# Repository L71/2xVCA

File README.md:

2 channel VCA module for Eurorack. 

LM13700 based VCA. Two separate channels. 
The VCA CV input is biased to about 8V when no plug is in the CV input (so VCA is open). 

This PCB and front panel drawings are released under the Creative Commons CC-BY-SA 4.0 license.

** Note: the SMD version of the module has the potentionmeters in the opposite direction of the usual. Use knobs that match (or pots with round or T18 shafts).

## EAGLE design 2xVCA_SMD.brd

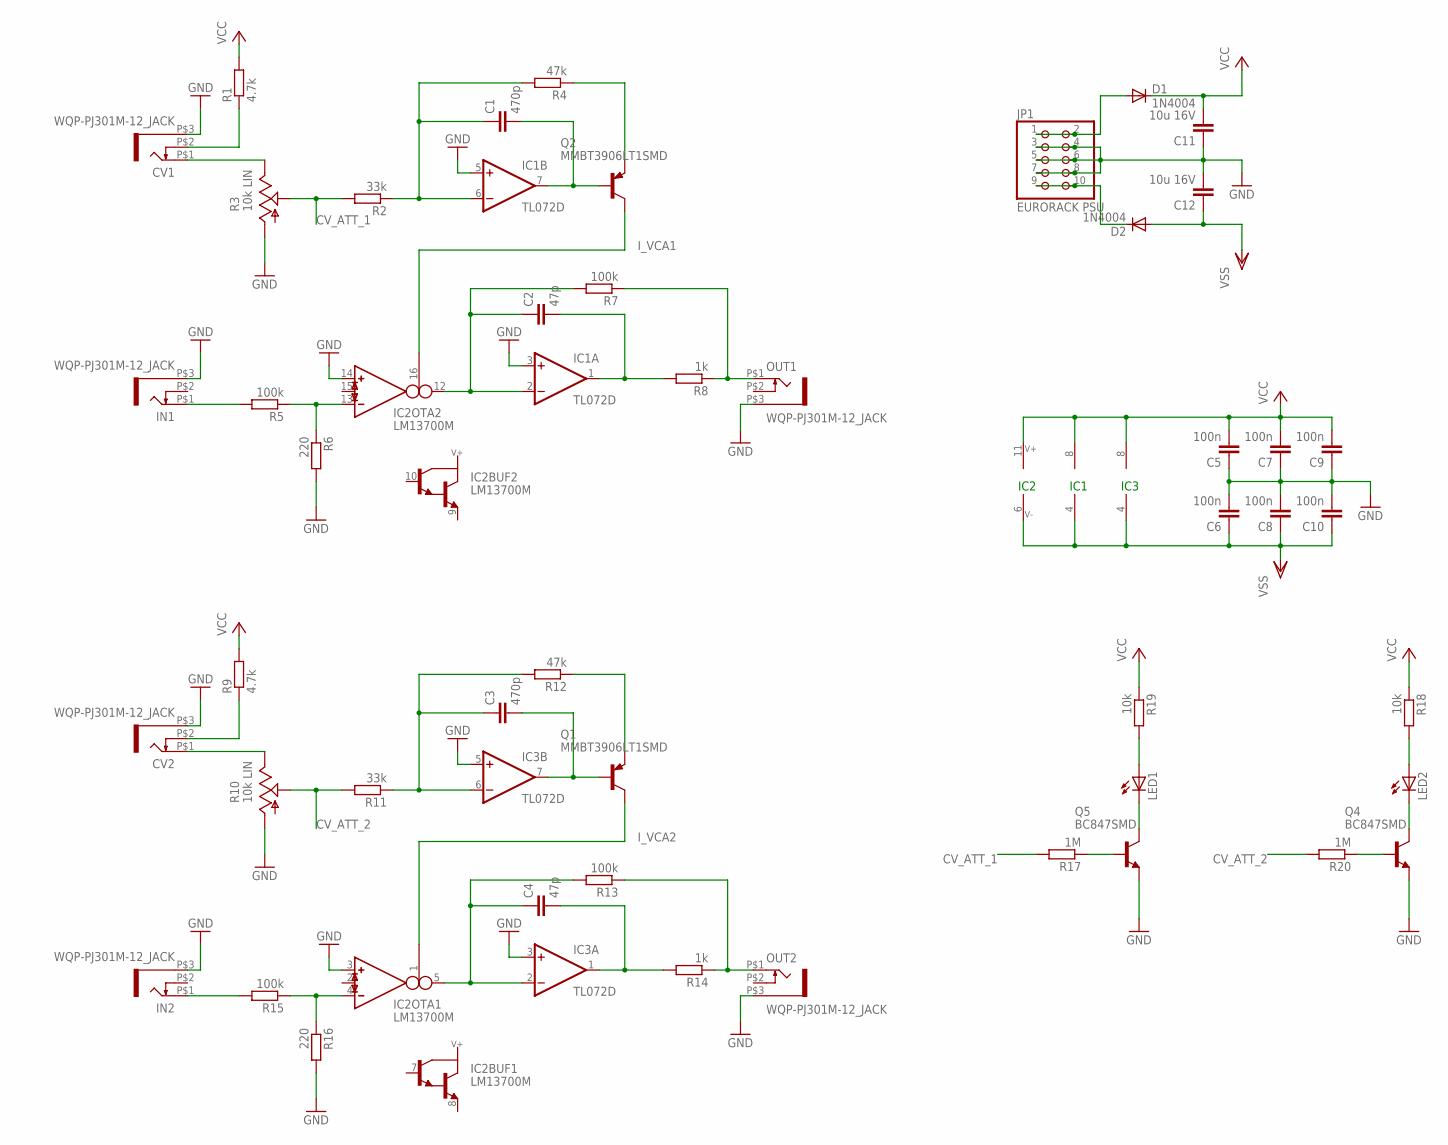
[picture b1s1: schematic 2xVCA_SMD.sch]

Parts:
C1, C3: 470p; C0603K
C2, C4: 47p; C0603K
C5, C6, C7, C8, C9, C10: 100n; C0603K
C11, C12: 10u 16V; C1206K
CV1, CV2: WQP-PJ301M-12_JACK
D1, D2: 1N4004; DO214AA
IC1, IC3: TL072D; SO08
IC2: LM13700M; SO16
IN1, IN2: WQP-PJ301M-12_JACK
JP1: EURORACK PSU; 2X05
LED1, LED2: LED3MM
OUT1, OUT2: WQP-PJ301M-12_JACK
Q1, Q2: MMBT3906LT1SMD; SOT23-BEC
Q4, Q5: BC847SMD; SOT23
R1, R9: 4.7k; R0603
R2, R11: 33k; R0603
R3, R10: 10k LIN; ALPS_POT_VERTICAL
R4, R12: 47k; R0603
R5, R7, R13, R15: 100k; R0603
R6, R16: 220; R0603
R8, R14: 1k; R0603
R17, R20: 1M; R0603
R18, R19: 10k; R0603

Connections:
CV_ATT_1: R2.2, R3.P$2 (S), R17.2
CV_ATT_2: R10.P$2 (S), R11.2, R20.2
GND: C5.1, C6.2, C7.1, C8.2, C9.1, C10.2, C11.1, C12.2, CV1.P$3 (1), CV2.P$3 (1), IC1.3 (+IN), IC1.5 (+IN), IC2.3 (IN_P), IC2.14 (IN_P), IC3.3 (+IN), IC3.5 (+IN), IN1.P$3 (1), IN2.P$3 (1), JP1.3, JP1.4, JP1.5, JP1.6, JP1.7, JP1.8, OUT1.P$3 (1), OUT2.P$3 (1), Q4.2 (E), Q5.2 (E), R3.P$3 (A), R6.2, R10.P$3 (A), R16.2
I_VCA1: IC2.16 (I_BIAS), Q2.C
I_VCA2: IC2.1 (I_BIAS), Q1.C
unnamed: IN2.P$1 (2), R15.2
unnamed: CV1.P$2 (3), R1.1
unnamed: CV1.P$1 (2), R3.P$1 (E)
unnamed: Q5.1 (B), R17.1
unnamed: C1.1, IC1.6 (-IN), R2.1, R4.2
unnamed: C2.1, IC1.2 (-IN), IC2.12 (OUT), R7.2
unnamed: C1.2, IC1.7 (OUT), Q2.B
unnamed: Q2.E, R4.1
unnamed: IC2.13 (IN_N), R5.1, R6.1
unnamed: IC2.4 (IN_N), R15.1, R16.1
unnamed: IN1.P$1 (2), R5.2
unnamed: C2.2, IC1.1 (OUT), R8.2
unnamed: OUT1.P$1 (2), R7.1, R8.1
unnamed: C4.1, IC2.5 (OUT), IC3.2 (-IN), R13.2
unnamed: CV2.P$2 (3), R9.1
unnamed: CV2.P$1 (2), R10.P$1 (E)
unnamed: LED1.A, R19.2
unnamed: C3.1, IC3.6 (-IN), R11.1, R12.2
unnamed: OUT2.P$1 (2), R13.1, R14.1
unnamed: C3.2, IC3.7 (OUT), Q1.B
unnamed: Q1.E, R12.1
unnamed: C4.2, IC3.1 (OUT), R14.2
unnamed: LED1.K (C), Q5.3 (C)
unnamed: LED2.A, R18.2
unnamed: LED2.K (C), Q4.3 (C)
unnamed: Q4.1 (B), R20.1
unnamed: D1.A, JP1.1, JP1.2
unnamed: D2.C, JP1.9, JP1.10
VCC: C5.2, C7.2, C9.2, C11.2, D1.C, IC1.8 (V+), IC2.11 (V+), IC3.8 (V+), R1.2, R9.2, R18.1, R19.1
VSS: C6.1, C8.1, C10.1, C12.1, D2.A, IC1.4 (V-), IC2.6 (V-), IC3.4 (V-)

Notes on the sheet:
IC1
IC2
IC3

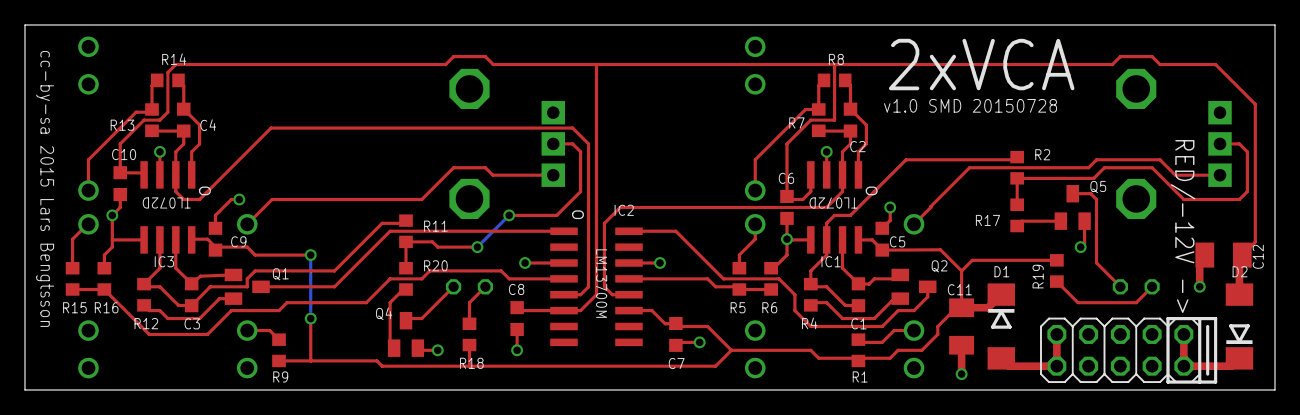
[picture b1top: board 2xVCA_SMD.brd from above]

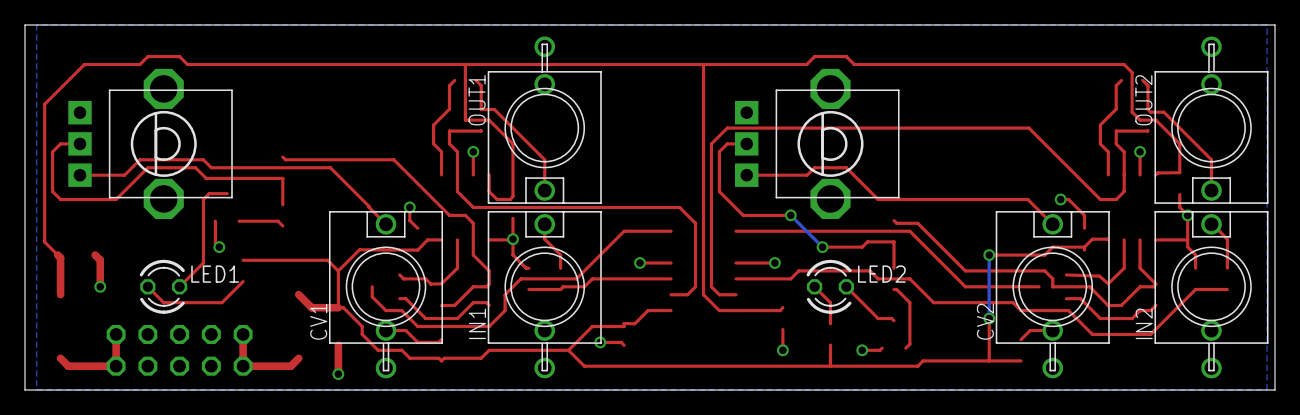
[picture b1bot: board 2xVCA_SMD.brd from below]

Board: 2 copper layers, 100.0 x 29.2 mm, 50 parts (10 on the bottom side), 35 nets.

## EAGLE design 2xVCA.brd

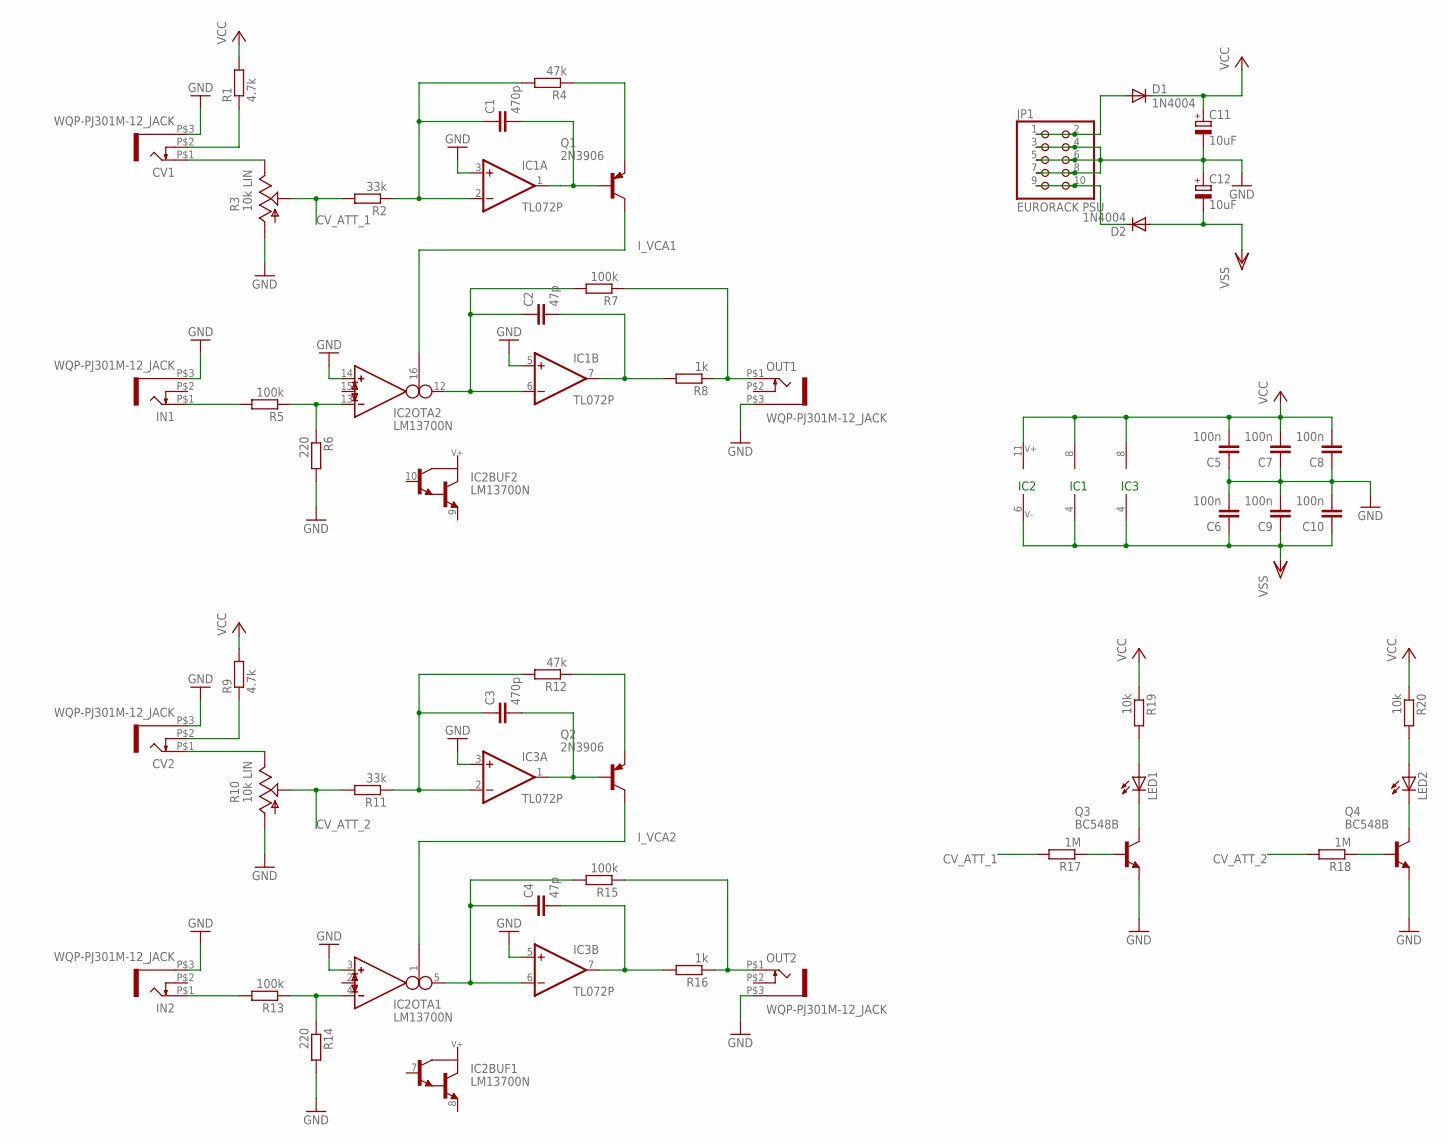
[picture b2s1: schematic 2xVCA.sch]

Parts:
C1, C3: 470p; C025-025X050
C2, C4: 47p; C025-025X050
C5, C6, C7, C8, C9, C10: 100n; C025-025X050
C11, C12: 10uF; E2,5-5
CV1, CV2: WQP-PJ301M-12_JACK
D1, D2: 1N4004; DO41-10
IC1, IC3: TL072P; DIL08
IC2: LM13700N; DIL16
IN1, IN2: WQP-PJ301M-12_JACK
JP1: EURORACK PSU; 2X05
LED1, LED2: LED3MM
OUT1, OUT2: WQP-PJ301M-12_JACK
Q1, Q2: 2N3906; TO92
Q3, Q4: BC548B; TO92-EBC
R1, R9: 4.7k; 0207/2V
R2, R11: 33k; 0207/2V
R3, R10: 10k LIN; ALPS_POT_VERTICAL
R4, R12: 47k; 0207/2V
R5, R7, R13, R15: 100k; 0207/2V
R6, R14: 220; 0207/2V
R8, R16: 1k; 0207/2V
R17, R18: 1M; 0207/2V
R19, R20: 10k; 0207/2V

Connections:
CV_ATT_1: R2.2, R3.P$2 (S), R17.2
CV_ATT_2: R10.P$2 (S), R11.2, R18.2
GND: C5.1, C6.2, C7.1, C8.1, C9.2, C10.2, C11.-, C12.+, CV1.P$3 (1), CV2.P$3 (1), IC1.3 (+IN), IC1.5 (+IN), IC2.3 (IN_P), IC2.14 (IN_P), IC3.3 (+IN), IC3.5 (+IN), IN1.P$3 (1), IN2.P$3 (1), JP1.3, JP1.4, JP1.5, JP1.6, JP1.7, JP1.8, OUT1.P$3 (1), OUT2.P$3 (1), Q3.E, Q4.E, R3.P$3 (A), R6.2, R10.P$3 (A), R14.2
I_VCA1: IC2.16 (I_BIAS), Q1.1 (C)
I_VCA2: IC2.1 (I_BIAS), Q2.1 (C)
unnamed: IN2.P$1 (2), R13.2
unnamed: CV1.P$2 (3), R1.1
unnamed: CV1.P$1 (2), R3.P$1 (E)
unnamed: Q3.B, R17.1
unnamed: C1.1, IC1.2 (-IN), R2.1, R4.2
unnamed: C2.1, IC1.6 (-IN), IC2.12 (OUT), R7.2
unnamed: C1.2, IC1.1 (OUT), Q1.2 (B)
unnamed: Q1.3 (E), R4.1
unnamed: IC2.13 (IN_N), R5.1, R6.1
unnamed: IC2.4 (IN_N), R13.1, R14.1
unnamed: IN1.P$1 (2), R5.2
unnamed: C2.2, IC1.7 (OUT), R8.2
unnamed: OUT1.P$1 (2), R7.1, R8.1
unnamed: C4.1, IC2.5 (OUT), IC3.6 (-IN), R15.2
unnamed: CV2.P$2 (3), R9.1
unnamed: CV2.P$1 (2), R10.P$1 (E)
unnamed: LED1.A, R19.2
unnamed: C3.1, IC3.2 (-IN), R11.1, R12.2
unnamed: OUT2.P$1 (2), R15.1, R16.1
unnamed: C3.2, IC3.1 (OUT), Q2.2 (B)
unnamed: Q2.3 (E), R12.1
unnamed: C4.2, IC3.7 (OUT), R16.2
unnamed: LED1.K (C), Q3.C
unnamed: LED2.A, R20.2
unnamed: LED2.K (C), Q4.C
unnamed: Q4.B, R18.1
unnamed: D1.A, JP1.1, JP1.2
unnamed: D2.C, JP1.9, JP1.10
VCC: C5.2, C7.2, C8.2, C11.+, D1.C, IC1.8 (V+), IC2.11 (V+), IC3.8 (V+), R1.2, R9.2, R19.1, R20.1
VSS: C6.1, C9.1, C10.1, C12.-, D2.A, IC1.4 (V-), IC2.6 (V-), IC3.4 (V-)

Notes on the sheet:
IC1
IC2
IC3

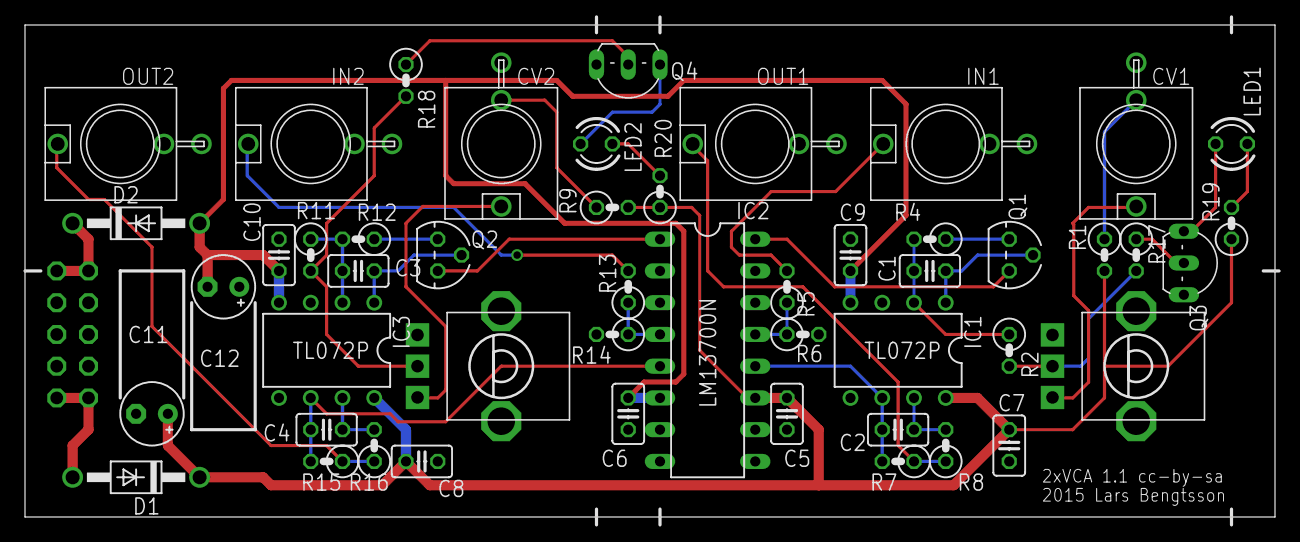
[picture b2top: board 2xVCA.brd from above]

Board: 2 copper layers, 100.0 x 39.4 mm, 50 parts (1 on the bottom side), 35 nets.

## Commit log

2015-03-23 Initial add.
2015-03-23 Added draft of panel file.
2015-03-23 Moved holes etc up 1/10" (ensure clearance between bottom end of PCB and lower rack rail).
2015-03-25 Initial front panel design completed.
2015-03-25 Added description.
2015-03-29 Added frame at output jacks and moved the text a bit.
2015-04-10 Updated after prototype built.
2015-04-10 Rotated CV input jacks and moved the LEDs a bit. Looks nicer this way.
2015-04-11 Updated component values for use with 10k potentiometers.
2015-07-28 Initial commit, SMD version, otherwise functinally and electrically identical (6HE wide).
2015-07-28 Fixed component labels. Minor routing adjustments. Spread PSU components a bit. Added board type label & copyright notice.
2015-07-28 Minor routing fixes. Adjusted labels a bit.
2015-07-28 Rotated T19 to match the rest :)
2015-07-29 Added panel. 6HP wide for SMD version of module. Follows Ponoko.com design guidelines.
2015-07-29 Added note about new SMD version potentiometers.
2016-01-11 Moved panel bottom edge and holes downwards 1/40" to better fit into racks w 3mm screws. Added engraving indicating the LEDs.

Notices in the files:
2xVCA.brd:
2xVCA 1.1 cc-by-sa
2xVCA_SMD.brd:
cc-by-sa 2015 Lars Bengtsson
